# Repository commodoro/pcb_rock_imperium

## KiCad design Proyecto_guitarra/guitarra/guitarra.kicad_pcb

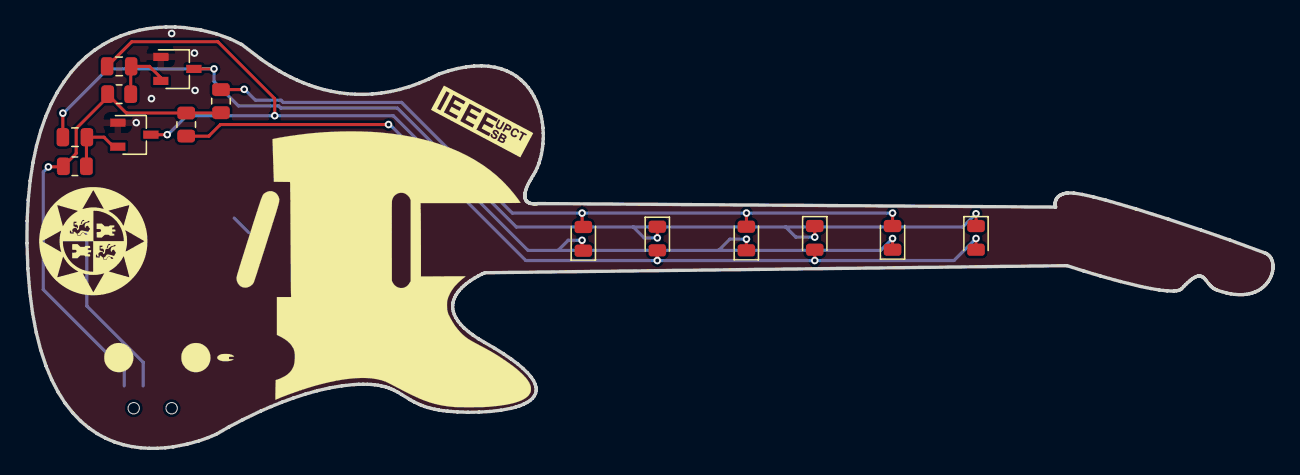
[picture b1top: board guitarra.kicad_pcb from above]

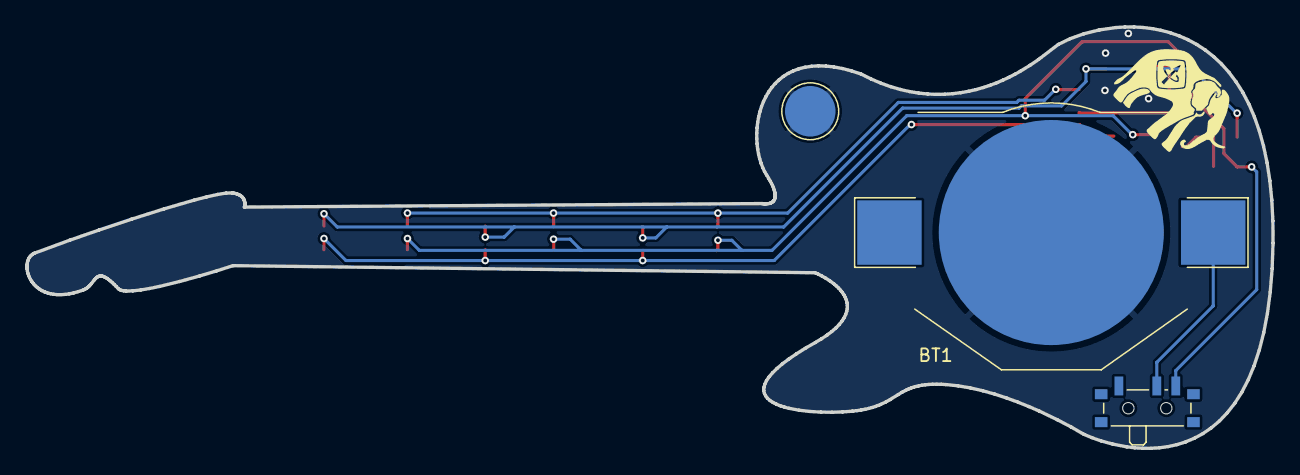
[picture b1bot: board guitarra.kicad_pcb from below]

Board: 2 copper layers, 98.5 x 33.3 mm, 18 parts (2 on the bottom side), 9 nets.

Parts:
BT1: Battery_Cell; BatteryHolder_Keystone_3002_1x2032
C1, C2: 10uF; C_0805_2012Metric
D1, D2, D3, D4, D5, D6: LED; LED_0805_2012Metric
Q1, Q2: 2N3904; TSOT-23
R1, R2: 1K; R_0805_2012Metric
R3, R4: 82K; R_0805_2012Metric
Ref**: Val**; metal
Ref**#2: Val**; serigrafia
SW1: SW_SPDT; SW_SPDT_PCM12

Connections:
+3V0: BT1.1 (+), SW1.2 (B)
/chr_a: C1.2, Q2.2 (B), R3.2
/chr_b: C2.2, Q1.2 (B), R4.2
/k_a: C2.1, D4.1 (K), D5.1 (K), D6.1 (K), Q2.3 (C)
/k_b: C1.1, D1.1 (K), D2.1 (K), D3.1 (K), Q1.3 (C)
/leds_a: D4.2 (A), D5.2 (A), D6.2 (A), R2.2
/leds_b: D1.2 (A), D2.2 (A), D3.2 (A), R1.2
/sw_on: R1.1, R2.1, R3.1, R4.1, SW1.1 (C)
GND: BT1.2 (-), Q1.1 (E), Q2.1 (E)

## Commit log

2023-06-12 subido alvaro V1.0
2023-06-12 Actualizado esquema y añadido switch
2023-06-13 terminado a falta de revision
2023-06-15 terminado. Pendiente revision y pulir bateria
2023-06-15 actualizada guitarra
2023-06-15 drc superado
2023-06-15 creados gerbers
2023-06-15 release version
